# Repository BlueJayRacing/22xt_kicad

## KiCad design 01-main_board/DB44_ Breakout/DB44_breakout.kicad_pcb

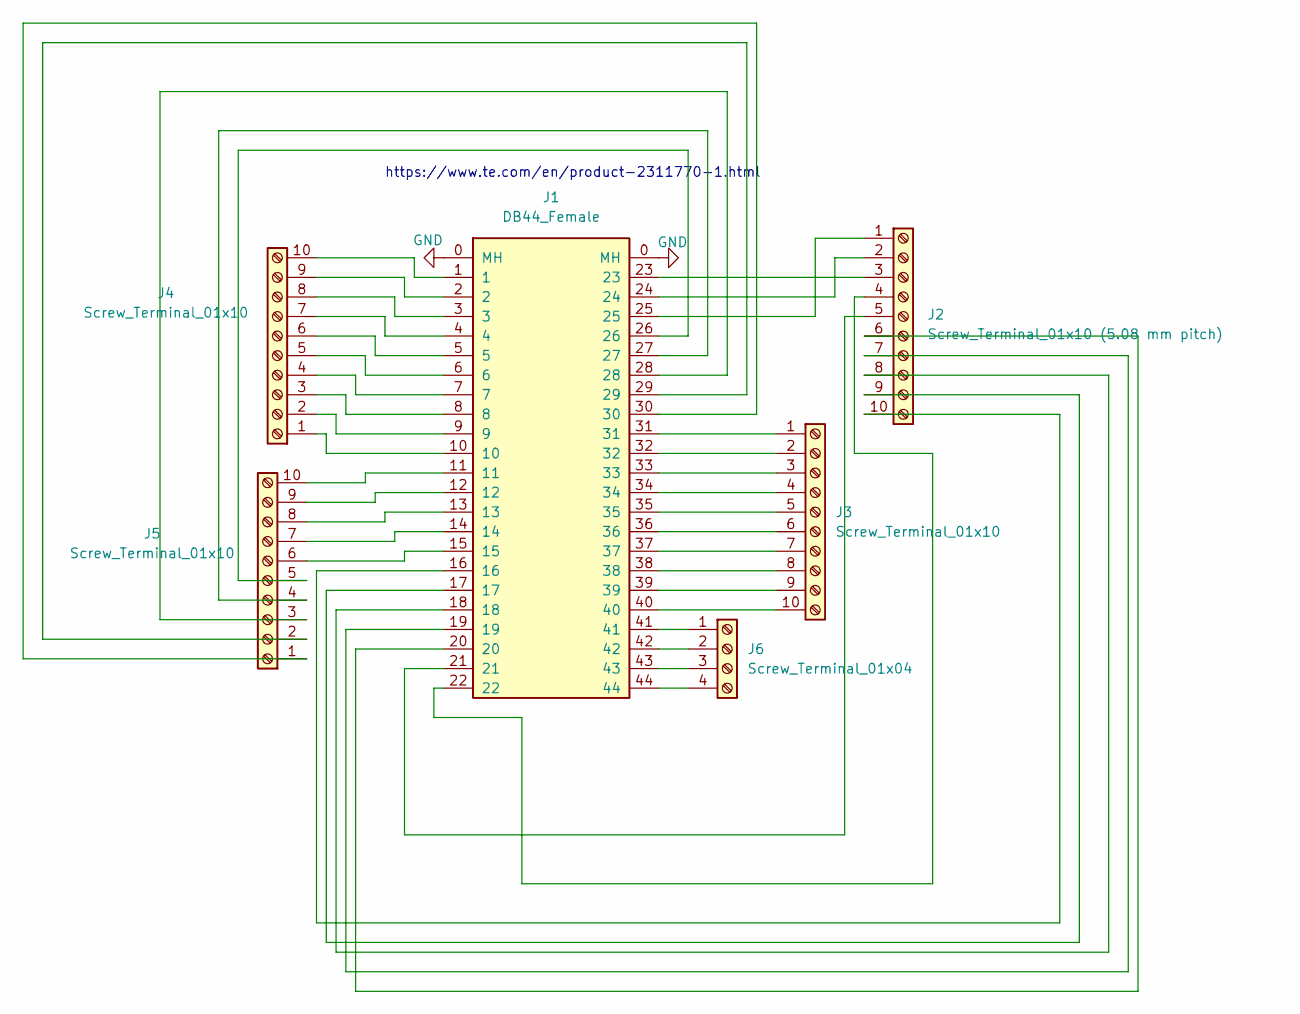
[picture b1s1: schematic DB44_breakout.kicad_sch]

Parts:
J1: DB44_Female; female-DB44-TE-2311770-1
J2: Screw_Terminal_01x10 (5.08 mm pitch); TerminalBlock_RND_205-00240_1x10_P5.08mm_Horizontal
J3, J4, J5: Screw_Terminal_01x10; TerminalBlock_RND_205-00240_1x10_P5.08mm_Horizontal
J6: Screw_Terminal_01x04; TerminalBlock_RND_205-00234_1x04_P5.08mm_Horizontal

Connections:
GND: J1.0 (MH)
unnamed: J1.25, J2.1
unnamed: J1.24, J2.2
unnamed: J1.23, J2.3
unnamed: J1.22, J2.4
unnamed: J1.21, J2.5
unnamed: J1.20, J2.6
unnamed: J1.19, J2.7
unnamed: J1.18, J2.8
unnamed: J1.17, J2.9
unnamed: J1.16, J2.10
unnamed: J1.31, J3.1
unnamed: J1.32, J3.2
unnamed: J1.33, J3.3
unnamed: J1.34, J3.4
unnamed: J1.35, J3.5
unnamed: J1.36, J3.6
unnamed: J1.37, J3.7
unnamed: J1.38, J3.8
unnamed: J1.39, J3.9
unnamed: J1.40, J3.10
unnamed: J1.10, J4.1
unnamed: J1.9, J4.2
unnamed: J1.8, J4.3
unnamed: J1.7, J4.4
unnamed: J1.6, J4.5
unnamed: J1.5, J4.6
unnamed: J1.4, J4.7
unnamed: J1.3, J4.8
unnamed: J1.2, J4.9
unnamed: J1.1, J4.10
unnamed: J1.30, J5.1
unnamed: J1.29, J5.2
unnamed: J1.28, J5.3
unnamed: J1.27, J5.4
unnamed: J1.26, J5.5
unnamed: J1.15, J5.6
unnamed: J1.14, J5.7
unnamed: J1.13, J5.8
unnamed: J1.12, J5.9
unnamed: J1.11, J5.10
unnamed: J1.41, J6.1
unnamed: J1.42, J6.2
unnamed: J1.43, J6.3
unnamed: J1.44, J6.4

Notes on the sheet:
https://www.te.com/en/product-2311770-1.html

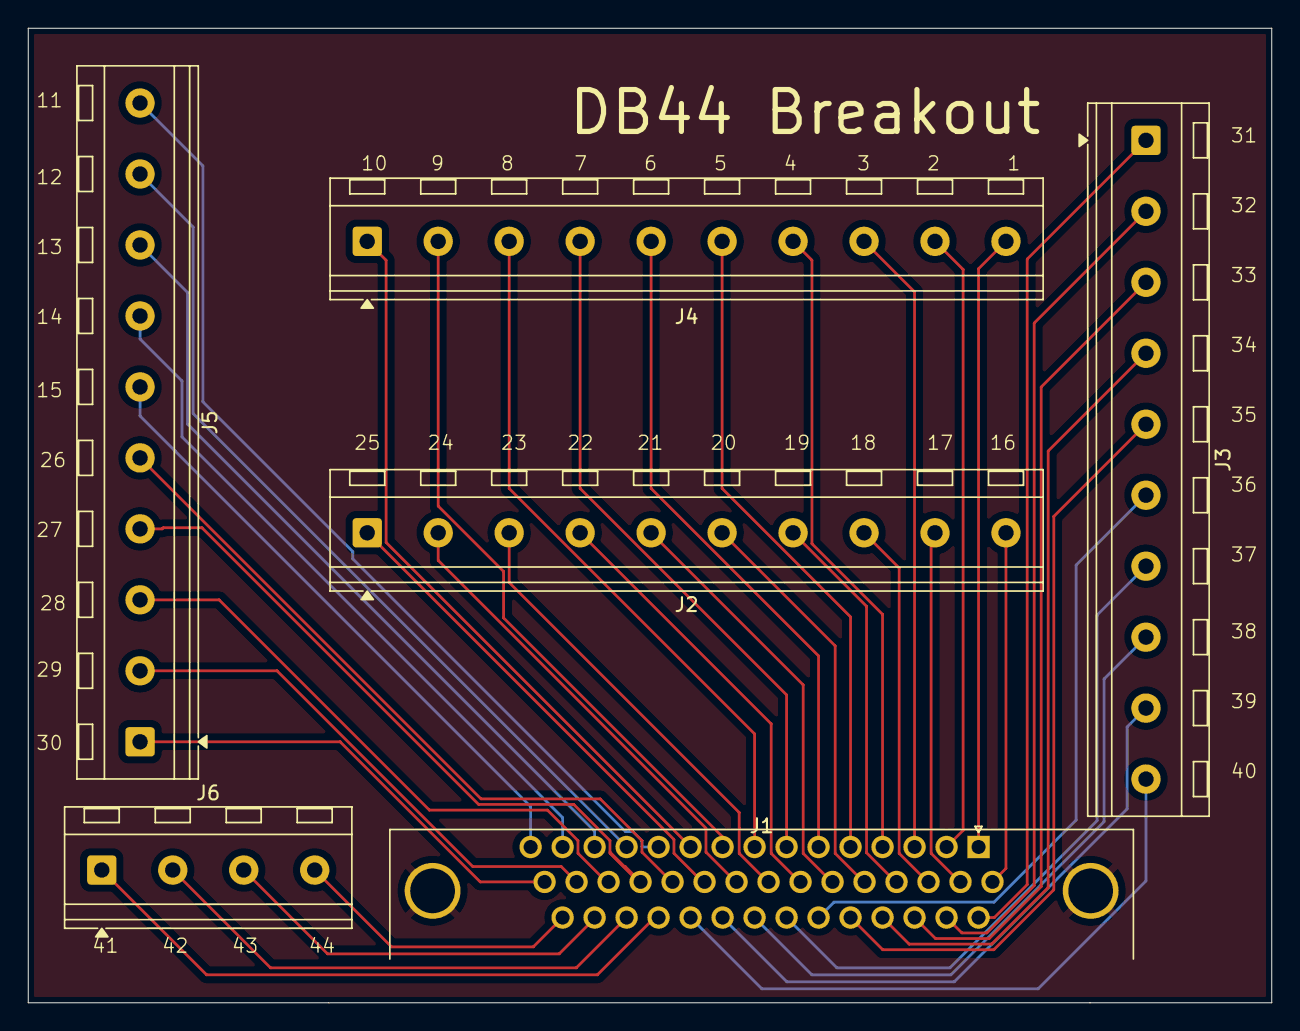
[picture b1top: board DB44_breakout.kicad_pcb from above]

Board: 2 copper layers, 89.0 x 69.8 mm, 6 parts (0 on the bottom side), 44 nets.

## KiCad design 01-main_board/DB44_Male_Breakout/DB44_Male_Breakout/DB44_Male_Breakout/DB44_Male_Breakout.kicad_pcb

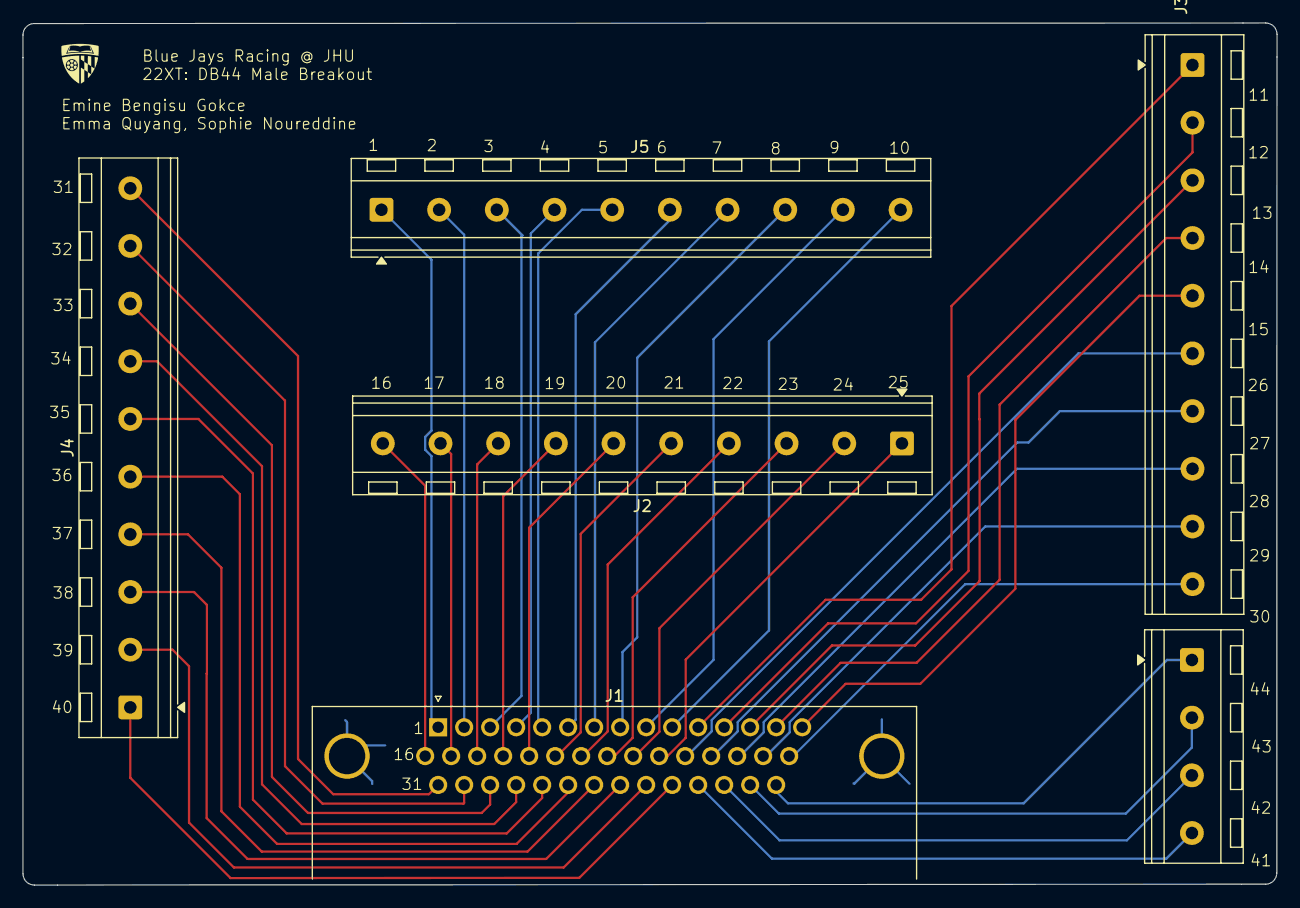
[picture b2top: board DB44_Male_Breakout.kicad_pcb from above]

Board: 2 copper layers, 110.4 x 75.9 mm, 6 parts (0 on the bottom side), 44 nets.

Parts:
J1: DB44_Male; DSUB-44-HD_Pins_Horizontal_P2.29x2.54mm_EdgePinOffset8.35mm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
J2, J3, J4, J5: Screw_Terminal_01x10; TerminalBlock_RND_205-00240_1x10_P5.08mm_Horizontal
J6: Screw_Terminal_01x04; TerminalBlock_RND_205-00234_1x04_P5.08mm_Horizontal

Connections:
3V3: J1.16, J2.10
3V3_T: J1.17, J2.9
5V: J1.35, J4.6
5V_1: J1.36, J4.5
5V_REF: J1.38, J4.3
11V1: J1.8, J5.8
11V1_1: J1.23, J2.3
AGND: J1.39, J4.2
AGND_1: J1.40, J4.1
AGND_2: J1.41, J6.4
AGND_3: J1.42, J6.3
AN1: J1.13, J3.3
AN2: J1.12, J3.2
AN3: J1.11, J3.1
AN4: J1.10, J5.10
AN5: J1.9, J5.9
AN6: J1.28, J3.8
AN7: J1.27, J3.7
AN8: J1.26, J3.6
AN9: J1.25, J2.1
AN10: J1.24, J2.2
B-: J1.37, J4.4
CANH: J1.1, J5.1
CANL: J1.2, J5.2
D1: J1.7, J5.7
D2: J1.6, J5.6
D3: J1.5, J5.5
D4: J1.22, J2.4
D5: J1.21, J2.5
D6: J1.20, J2.6
DGND: J1.31, J4.10
DGND_1: J1.32, J4.9
DGND_2: J1.33, J4.8
DGND_3: J1.34, J4.7
GP/LNT1: J1.19, J2.7
GP/LNT2: J1.18, J2.8
I2C_SCL: J1.3, J5.3
I2C_SDA: J1.4, J5.4
QS1+ (2V5R): J1.43, J6.2
QS1F-: J1.29, J3.9
QS1S-: J1.14, J3.4
QS2+ (2V5R): J1.44, J6.1
QS2F-: J1.30, J3.10
QS2S-: J1.15, J3.5

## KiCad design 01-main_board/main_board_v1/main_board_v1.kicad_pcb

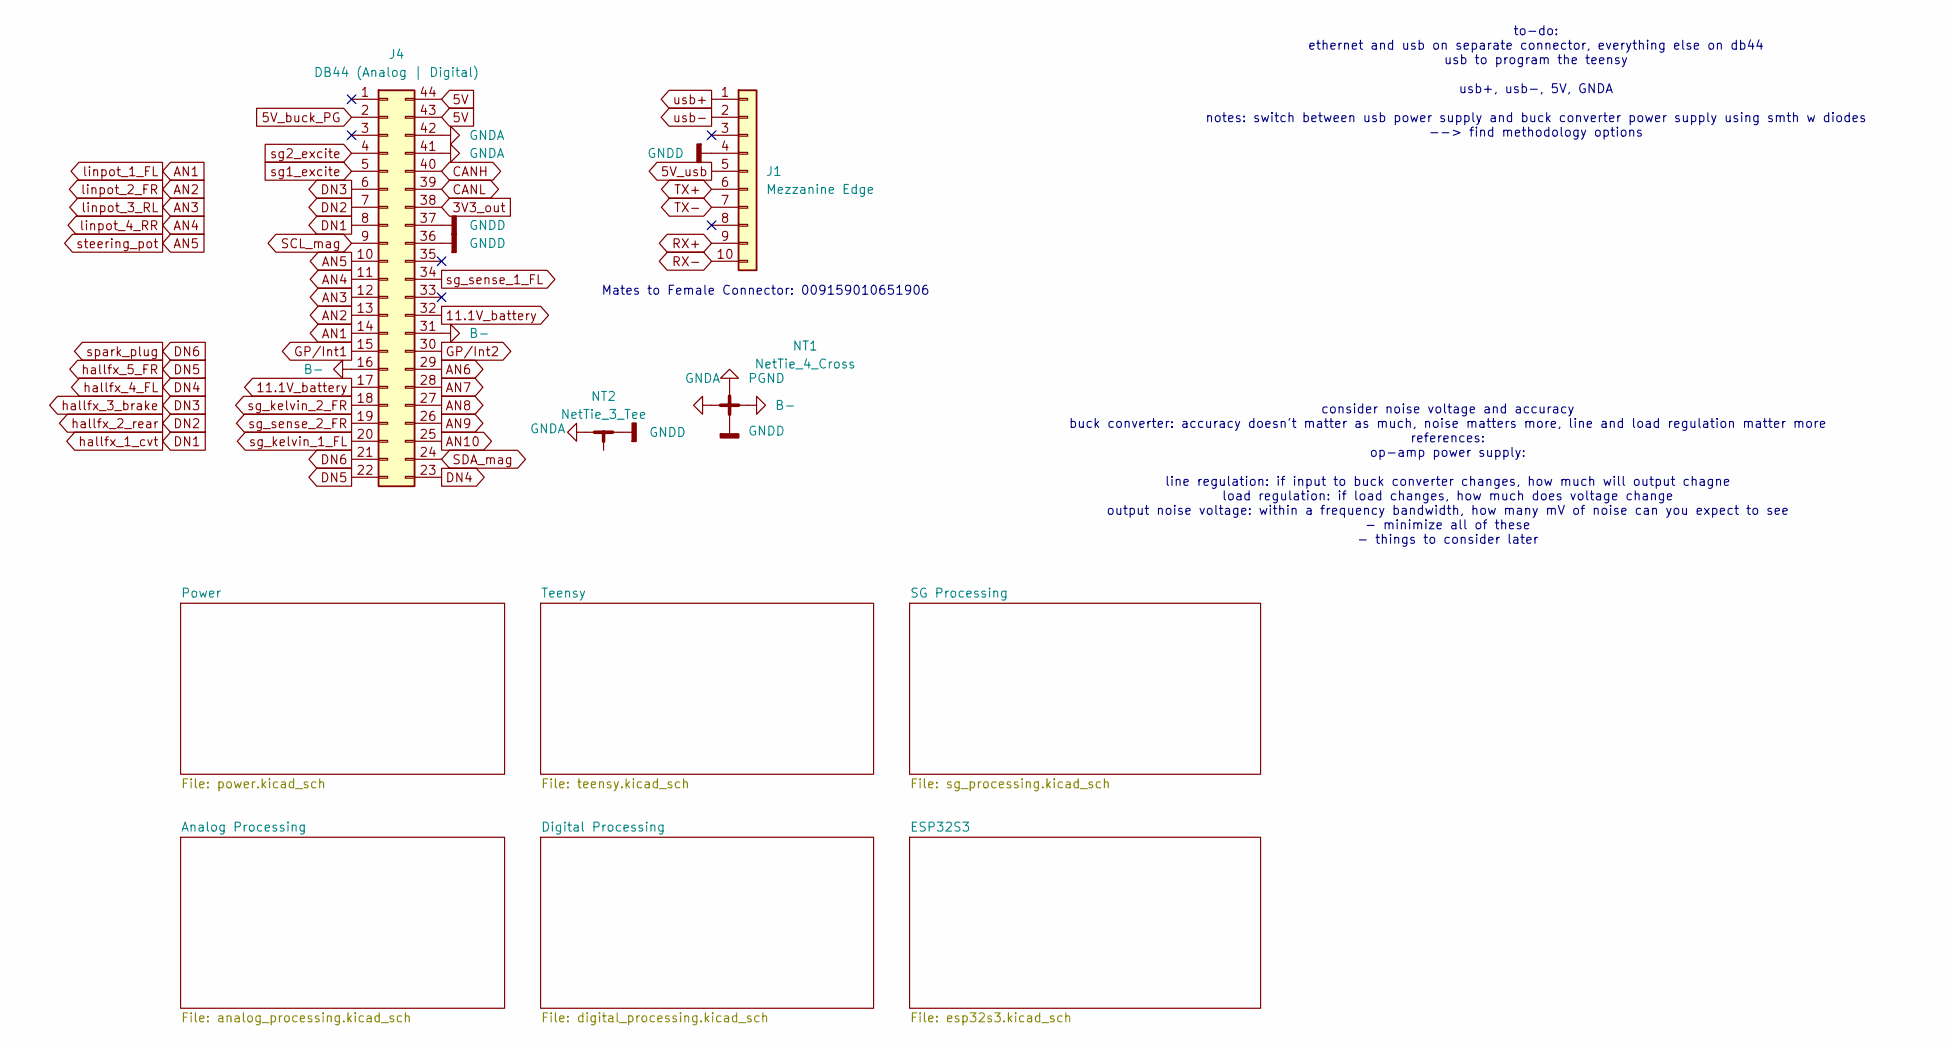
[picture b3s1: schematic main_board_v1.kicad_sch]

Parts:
J1: Mezzanine Edge; Double Sided Mezzanine Card Edge_Edge Side
J4: DB44 (Analog | Digital); aaren_mouser_db44_screws
NT1: NetTie_4_Cross; NetTie-4_SMD_Pad0.5mm
NT2: NetTie_3_Tee; NetTie-2_SMD_Pad0.5mm

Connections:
2V5: J4.4, J4.5; also elsewhere on the board
3V3_out: J4.38; also elsewhere on the board
5V: J4.43, J4.44; also elsewhere on the board
5V_buck_PG: J4.2; also elsewhere on the board
5V_usb: J1.5; also elsewhere on the board
11.1V_battery: J4.17, J4.32; also elsewhere on the board
AN1: J4.14; also elsewhere on the board
AN2: J4.13; also elsewhere on the board
AN3: J4.12; also elsewhere on the board
AN4: J4.11; also elsewhere on the board
AN5: J4.10; also elsewhere on the board
AN6: J4.29; also elsewhere on the board
AN7: J4.28; also elsewhere on the board
AN8: J4.27; also elsewhere on the board
AN9: J4.26; also elsewhere on the board
AN10: J4.25; also elsewhere on the board
B-: J4.16, J4.31, NT1.2
CANH: J4.40; also elsewhere on the board
CANL: J4.39; also elsewhere on the board
DN1: J4.8; also elsewhere on the board
DN2: J4.7; also elsewhere on the board
DN3: J4.6; also elsewhere on the board
DN4: J4.23; also elsewhere on the board
DN5: J4.22; also elsewhere on the board
DN6: J4.21; also elsewhere on the board
GP/Int1: J4.15; also elsewhere on the board
GP/Int2: J4.30; also elsewhere on the board
PGND: NT1.3; also elsewhere on the board
RX+: J1.9; also elsewhere on the board
RX-: J1.10; also elsewhere on the board
SCL_mag: J4.9; also elsewhere on the board
SDA_mag: J4.24; also elsewhere on the board
TX+: J1.6; also elsewhere on the board
TX-: J1.7; also elsewhere on the board
sg1+: J4.20; also elsewhere on the board
sg2+: J4.18; also elsewhere on the board
sg_sense_1_FL: J4.34; also elsewhere on the board
sg_sense_2_FR: J4.19; also elsewhere on the board
usb+: J1.1; also elsewhere on the board
usb-: J1.2; also elsewhere on the board

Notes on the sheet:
consider noise voltage and accuracy buck converter: accuracy doesn't matter as much, noise matters more, line and load regulation matter more references: op-amp power supply: line regulation: if input to buck converter changes, how much will output chagne load regulation: if load changes, how much 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
to-do: ethernet and usb on separate connector, everything else on db44 usb to program the teensy usb+, usb-, 5V, GNDA notes: switch between usb power supply and buck converter power supply using smth w diodes --> find methodology options
Mates to Female Connector: 009159010651906

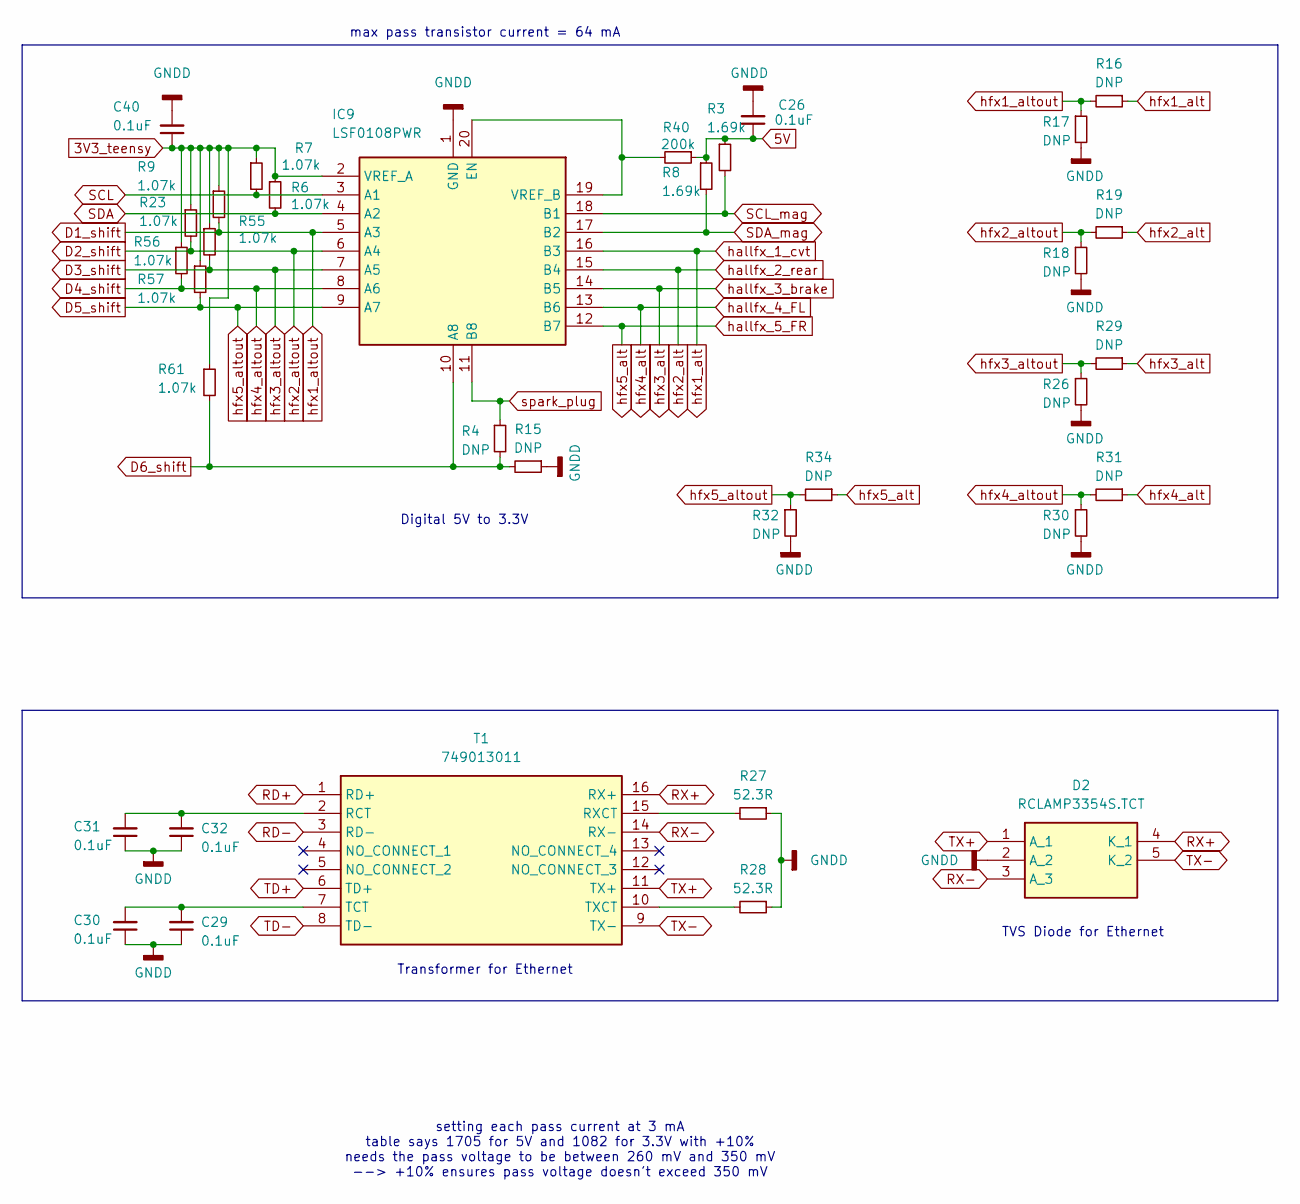
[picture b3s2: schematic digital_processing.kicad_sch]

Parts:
C26, C29, C30, C31, C32, C40: 0.1uF; C_0402_1005Metric
D2: RCLAMP3354S.TCT; SOT-23-5; Mouser Part Number 947-RCLAMP3354S.TCT
IC9: LSF0108PWR; SOP65P640X120-20N; Mouser Part Number 595-LSF0108RKSR
R3, R8: 1.69k; R_0402_1005Metric
R4, R15, R16, R17, R18, R19, R26, R29, R30, R31, R32, R34: DNP; R_0402_1005Metric
R6, R7, R9, R23, R55, R56, R57, R61: 1.07k; R_0402_1005Metric
R27, R28: 52.3R; R_0402_1005Metric
R40: 200k; R_0402_1005Metric
T1: 749013011; Mouser Part Number 710-749013011

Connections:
3V3_teensy: C40.1, IC9.2 (VREF_A), R6.1, R7.1, R9.1, R23.1, R55.1, R56.1, R57.1, R61.1; also elsewhere on the board
5V: C26.1, R3.1, R8.1, R40.1; also elsewhere on the board
D1_shift: IC9.5 (A3), R9.2, R16.2, R17.1; also elsewhere on the board
D2_shift: IC9.6 (A4), R18.1, R19.2, R23.2; also elsewhere on the board
D3_shift: IC9.7 (A5), R26.1, R29.2, R55.2; also elsewhere on the board
D4_shift: IC9.8 (A6), R30.1, R31.2, R56.2; also elsewhere on the board
D5_shift: IC9.9 (A7), R32.1, R34.2, R57.2; also elsewhere on the board
D6_shift: IC9.10 (A8), R4.2, R15.2, R61.2; also elsewhere on the board
DN1: IC9.16 (B3), R16.1; also elsewhere on the board
DN2: IC9.15 (B4), R19.1; also elsewhere on the board
DN3: IC9.14 (B5), R29.1; also elsewhere on the board
DN4: IC9.13 (B6), R31.1; also elsewhere on the board
DN5: IC9.12 (B7), R34.1; also elsewhere on the board
DN6: IC9.11 (B8), R4.1; also elsewhere on the board
unnamed: IC9.19 (VREF_B), IC9.20 (EN), R40.2
unnamed: C31.2, C32.2, T1.2 (RCT)
unnamed: R27.2, T1.15 (RXCT)
unnamed: C29.2, C30.2, T1.7 (TCT)
unnamed: R28.2, T1.10 (TXCT)
RD+: T1.1 (RD+); also elsewhere on the board
RD-: T1.3 (RD-); also elsewhere on the board
RX+: D2.4 (K_1), T1.16 (RX+); also elsewhere on the board
RX-: D2.3 (A_3), T1.14 (RX-); also elsewhere on the board
SCL: IC9.3 (A1), R7.2; also elsewhere on the board
SCL_mag: IC9.18 (B1), R3.2; also elsewhere on the board
SDA: IC9.4 (A2), R6.2; also elsewhere on the board
SDA_mag: IC9.17 (B2), R8.2; also elsewhere on the board
TD+: T1.6 (TD+); also elsewhere on the board
TD-: T1.8 (TD-); also elsewhere on the board
TX+: D2.1 (A_1), T1.11 (TX+); also elsewhere on the board
TX-: D2.5 (K_2), T1.9 (TX-); also elsewhere on the board

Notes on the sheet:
Transformer for Ethernet
max pass transistor current = 64 mA
Digital 5V to 3.3V
TVS Diode for Ethernet
setting each pass current at 3 mA table says 1705 for 5V and 1082 for 3.3V with +10% needs the pass voltage to be between 260 mV and 350 mV --> +10% ensures pass voltage doesn't exceed 350 mV

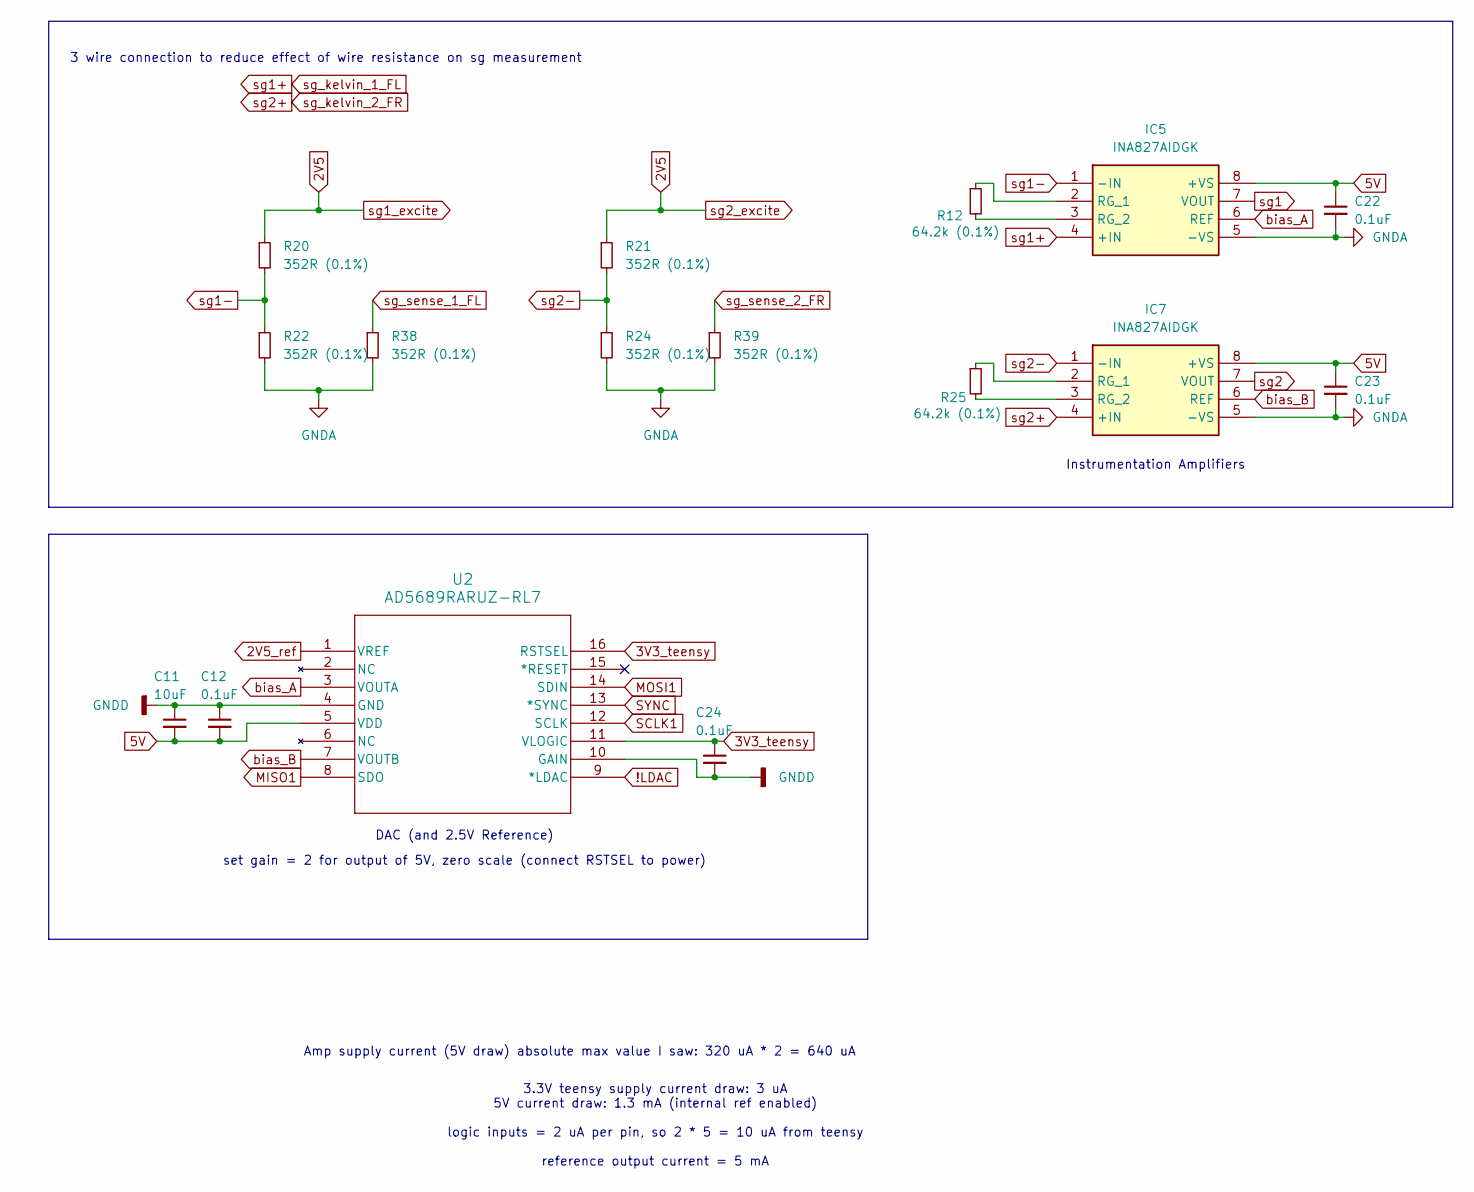
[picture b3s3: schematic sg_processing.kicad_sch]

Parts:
C11: 10uF; C_0402_1005Metric
C12, C22, C23, C24: 0.1uF; C_0402_1005Metric
IC5, IC7: INA827AIDGK; Mouser Part Number 595-INA827AIDGK
R12, R25: 64.2k (0.1%); R_0402_1005Metric
R20, R21, R22, R24, R38, R39: 352R (0.1%); R_0402_1005Metric
U2: AD5689RARUZ-RL7

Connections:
2V5: R20.1, R21.1; also elsewhere on the board
2V5_ref: U2.1 (VREF); also elsewhere on the board
3V3_teensy: C24.1, U2.11 (VLOGIC), U2.16 (RSTSEL); also elsewhere on the board
5V: C11.2, C12.2, C22.1, C23.1, IC5.8 (+VS), IC7.8 (+VS), U2.5 (VDD); also elsewhere on the board
!LDAC: U2.9 (*LDAC); also elsewhere on the board
MISO1: U2.8 (SDO); also elsewhere on the board
MOSI1: U2.14 (SDIN); also elsewhere on the board
unnamed: IC5.2 (RG_1), R12.1
unnamed: IC5.3 (RG_2), R12.2
unnamed: IC7.2 (RG_1), R25.1
unnamed: IC7.3 (RG_2), R25.2
SCLK1: U2.12 (SCLK); also elsewhere on the board
SYNC: U2.13 (*SYNC); also elsewhere on the board
bias_A: IC5.6 (REF), U2.3 (VOUTA)
bias_B: IC7.6 (REF), U2.7 (VOUTB)
sg1: IC5.7 (VOUT); also elsewhere on the board
sg1+: IC5.4 (+IN); also elsewhere on the board
sg1-: IC5.1 (-IN), R20.2, R22.1
sg2: IC7.7 (VOUT); also elsewhere on the board
sg2+: IC7.4 (+IN); also elsewhere on the board
sg2-: IC7.1 (-IN), R21.2, R24.1
sg_sense_1_FL: R38.1; also elsewhere on the board
sg_sense_2_FR: R39.1; also elsewhere on the board

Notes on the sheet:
DAC (and 2.5V Reference)
Amp supply current (5V draw) absolute max value I saw: 320 uA * 2 = 640 uA
3.3V teensy supply current draw: 3 uA 5V current draw: 1.3 mA (internal ref enabled) logic inputs = 2 uA per pin, so 2 * 5 = 10 uA from teensy reference output current = 5 mA
set gain = 2 for output of 5V, zero scale (connect RSTSEL to power)
Instrumentation Amplifiers
3 wire connection to reduce effect of wire resistance on sg measurement

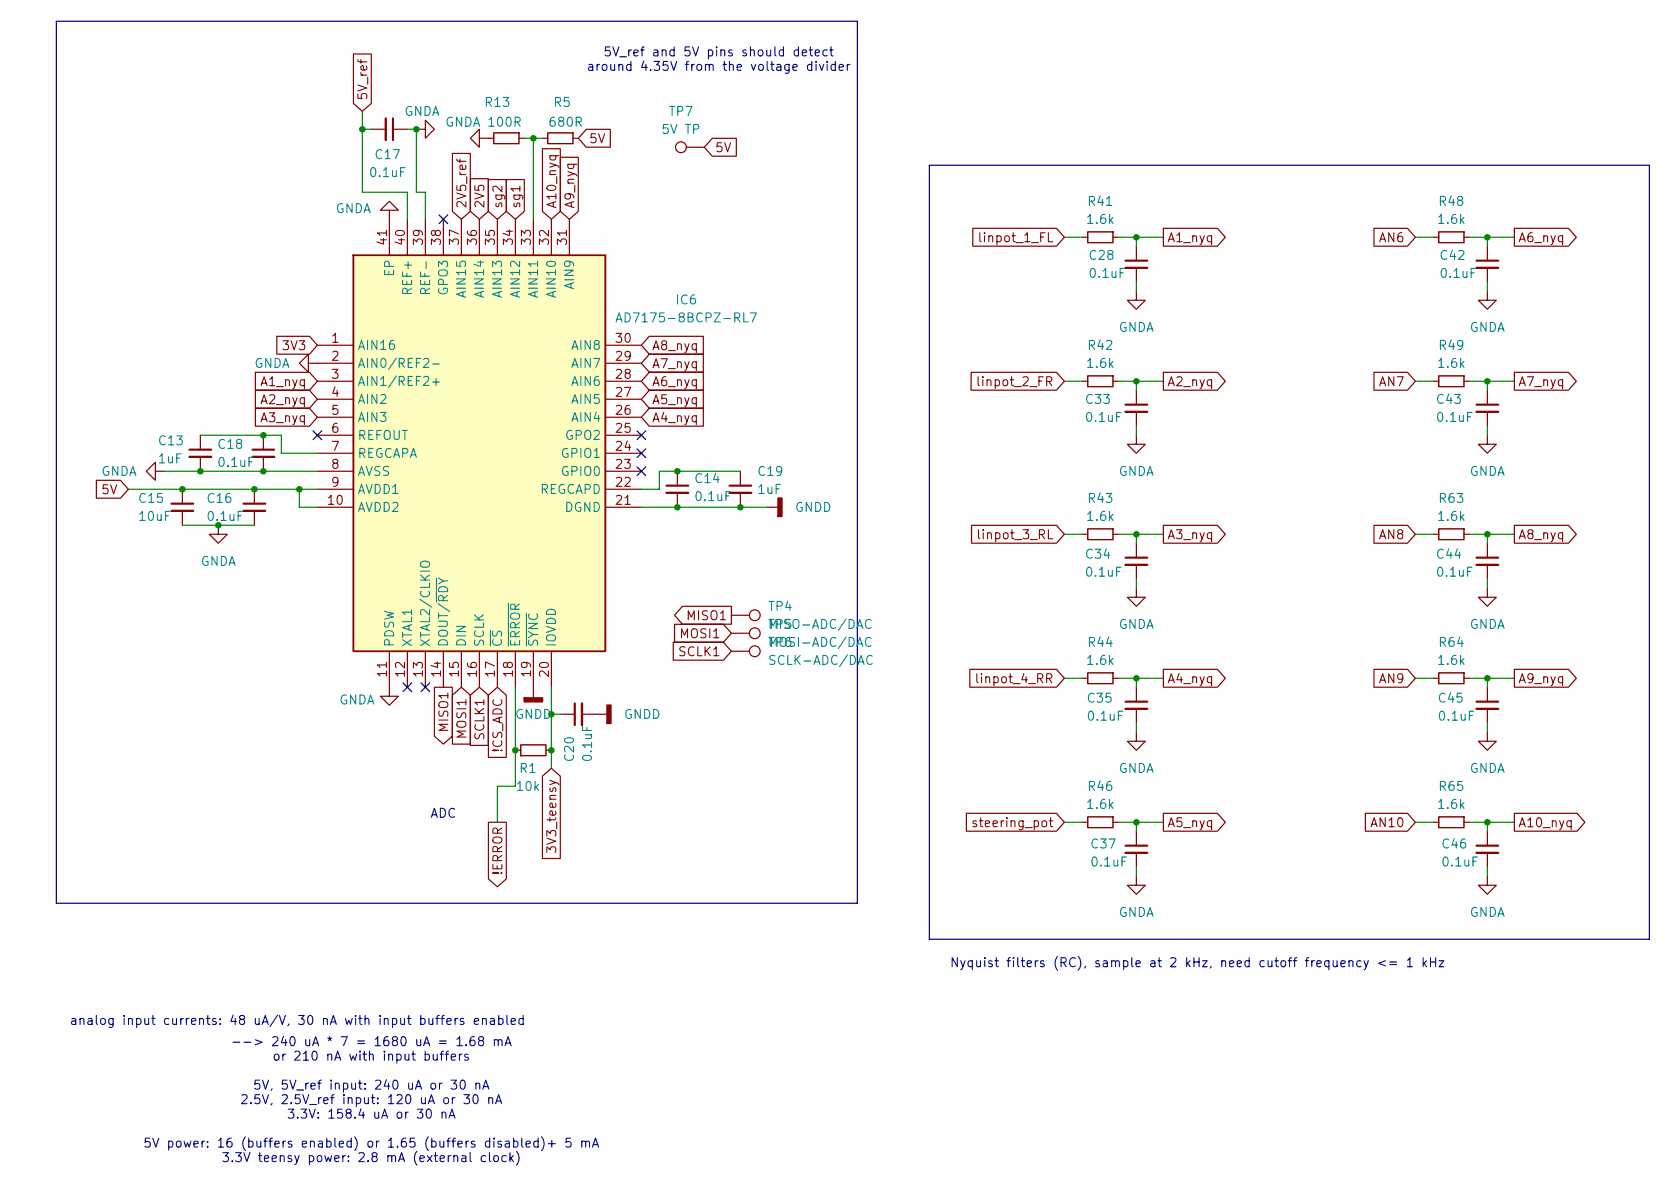
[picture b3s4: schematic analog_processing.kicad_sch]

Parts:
C13, C19: 1uF; C_0402_1005Metric
C14, C16, C17, C18, C20, C28, C33, C34, C35, C37, C42, C43, C44, C45, C46: 0.1uF; C_0402_1005Metric
C15: 10uF; C_0402_1005Metric
IC6: AD7175-8BCPZ-RL7; QFN50P600X600X80-41N-D; Mouser Part Number 584-AD7175-8BCPZ-RL7
R1: 10k; R_0402_1005Metric
R5: 680R; R_0402_1005Metric
R13: 100R; R_0402_1005Metric
R41, R42, R43, R44, R46, R48, R49, R63, R64, R65: 1.6k; R_0402_1005Metric
TP4: MISO-ADC/DAC; TestPoint_Pad_1.0x1.0mm
TP5: MOSI-ADC/DAC; TestPoint_Pad_1.0x1.0mm
TP6: SCLK-ADC/DAC; TestPoint_Pad_1.0x1.0mm
TP7: 5V TP; TestPoint_Pad_1.0x1.0mm

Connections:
2V5: IC6.36 (AIN14); also elsewhere on the board
2V5_ref: IC6.37 (AIN15); also elsewhere on the board
3V3: IC6.1 (AIN16); also elsewhere on the board
3V3_teensy: C20.1, IC6.20 (IOVDD), R1.2; also elsewhere on the board
5V: C15.1, C16.1, IC6.9 (AVDD1), IC6.10 (AVDD2), R5.1, TP7.1; also elsewhere on the board
5V_ref: C17.2, IC6.40 (REF+); also elsewhere on the board
!CS_ADC: IC6.17 (~CS); also elsewhere on the board
!ERROR: IC6.18 (~ERROR), R1.1; also elsewhere on the board
A1_nyq: C28.1, IC6.3 (AIN1/REF2+), R41.1
A2_nyq: C33.1, IC6.4 (AIN2), R42.1
A3_nyq: C34.1, IC6.5 (AIN3), R43.1
A4_nyq: C35.1, IC6.26 (AIN4), R44.1
A5_nyq: C37.1, IC6.27 (AIN5), R46.1
A6_nyq: C42.1, IC6.28 (AIN6), R48.1
A7_nyq: C43.1, IC6.29 (AIN7), R49.1
A8_nyq: C44.1, IC6.30 (AIN8), R63.1
A9_nyq: C45.1, IC6.31 (AIN9), R64.1
A10_nyq: C46.1, IC6.32 (AIN10), R65.1
AN1: R41.2; also elsewhere on the board
AN2: R42.2; also elsewhere on the board
AN3: R43.2; also elsewhere on the board
AN4: R44.2; also elsewhere on the board
AN5: R46.2; also elsewhere on the board
AN6: R48.2; also elsewhere on the board
AN7: R49.2; also elsewhere on the board
AN8: R63.2; also elsewhere on the board
AN9: R64.2; also elsewhere on the board
AN10: R65.2; also elsewhere on the board
MISO1: IC6.14 (DOUT/~RDY), TP4.1; also elsewhere on the board
MOSI1: IC6.15 (DIN), TP5.1; also elsewhere on the board
unnamed: IC6.33 (AIN11), R5.2, R13.1
unnamed: C13.1, C18.1, IC6.7 (REGCAPA)
unnamed: C14.1, C19.1, IC6.22 (REGCAPD)
SCLK1: IC6.16 (SCLK), TP6.1; also elsewhere on the board
sg1: IC6.34 (AIN12); also elsewhere on the board
sg2: IC6.35 (AIN13); also elsewhere on the board

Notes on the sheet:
ADC
--> 240 uA * 7 = 1680 uA = 1.68 mA or 210 nA with input buffers 5V, 5V_ref input: 240 uA or 30 nA 2.5V, 2.5V_ref input: 120 uA or 30 nA 3.3V: 158.4 uA or 30 nA 5V power: 16 (buffers enabled) or 1.65 (buffers disabled)+ 5 mA 3.3V teensy power: 2.8 mA (external clock)
analog input currents: 48 uA/V, 30 nA with input buffers enabled
Nyquist filters (RC), sample at 2 kHz, need cutoff frequency <= 1 kHz
5V_ref and 5V pins should detect around 4.35V from the voltage divider

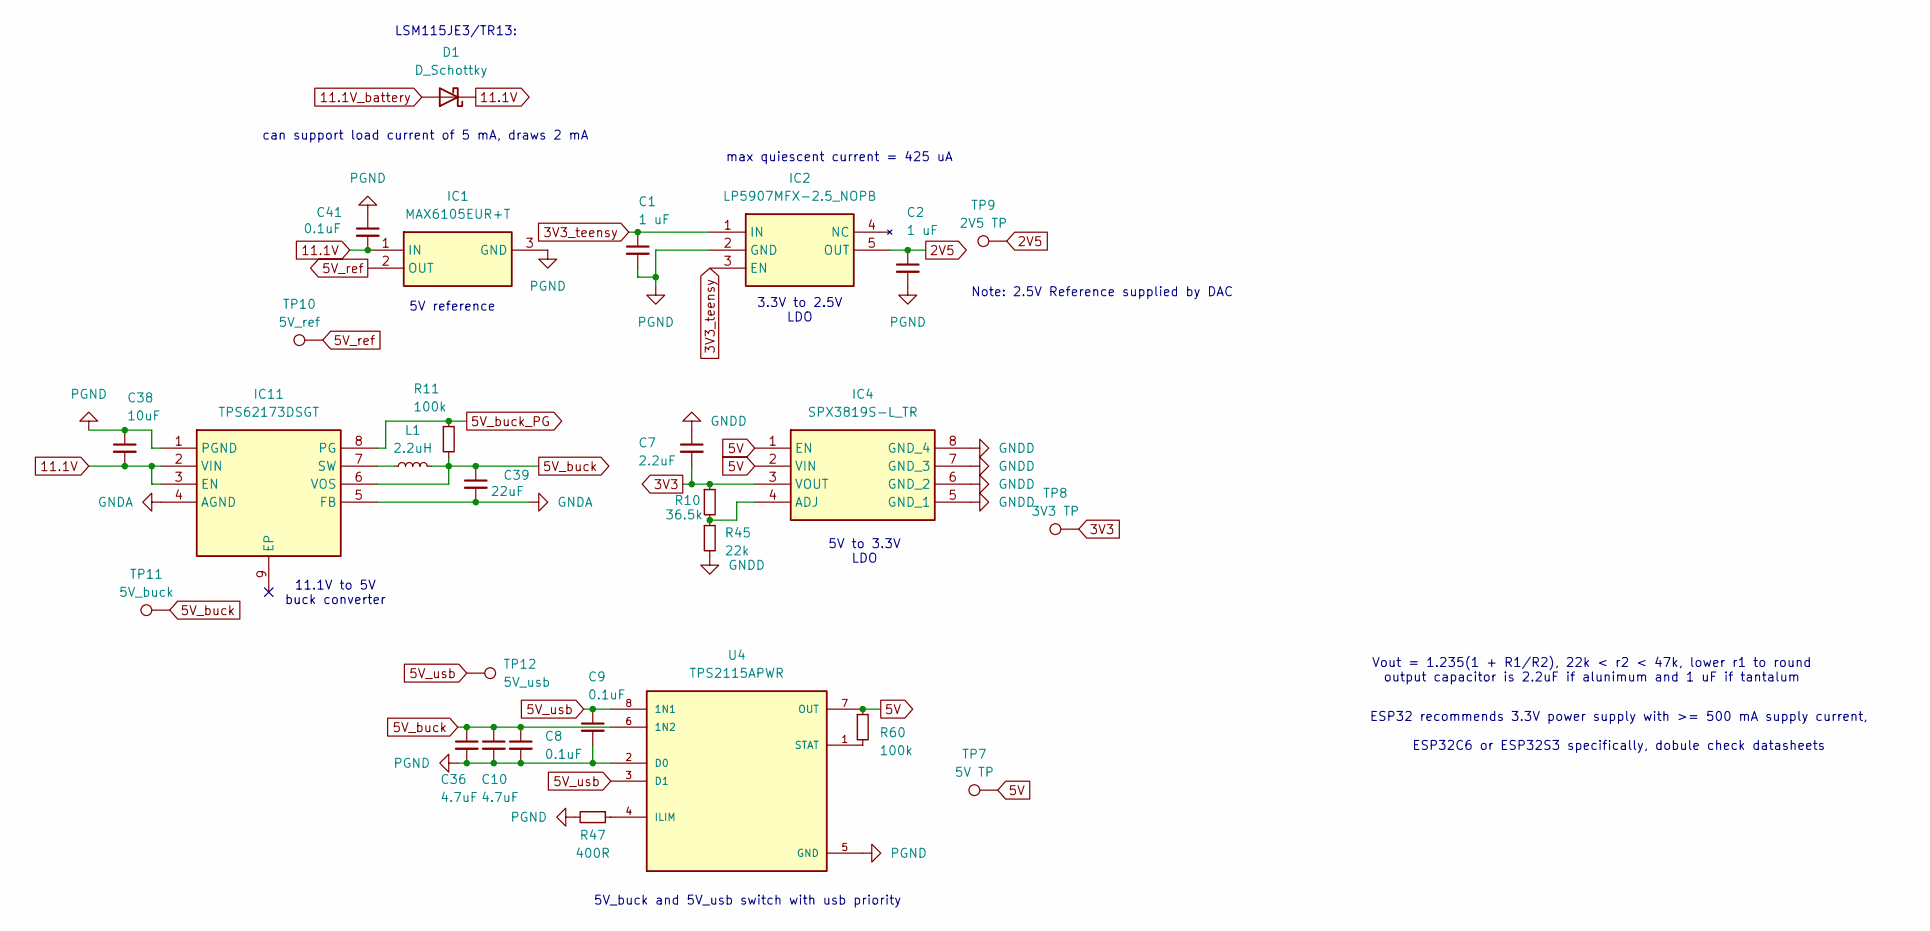
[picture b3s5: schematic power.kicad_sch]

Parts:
C1, C2: 1 uF; C_0402_1005Metric
C7: 2.2uF; C_0402_1005Metric
C8, C9, C41: 0.1uF; C_0402_1005Metric
C10, C36: 4.7uF; C_0402_1005Metric
C38: 10uF; C_0402_1005Metric
C39: 22uF; C_0402_1005Metric
D1: D_Schottky; DO-214BA_MCH
IC1: MAX6105EUR+T; SOT-23-3; Mouser Part Number 700-MAX6105EURT
IC2: LP5907MFX-2.5_NOPB; SOT-23-5; Mouser Part Number 595-LP5907MFX2.5NOPB
IC4: SPX3819S-L_TR; SOIC127P600X175-8N; Mouser Part Number 701-SPX3819S-L/TR
IC11: TPS62173DSGT; SON50P200X200X80-9N; Mouser Part Number 595-TPS62173DSGT
L1: 2.2uH; L_0402_1005Metric
R10: 36.5k; R_0402_1005Metric
R11, R60: 100k; R_0402_1005Metric
R45: 22k; R_0402_1005Metric
R47: 400R; R_0402_1005Metric
TP7: 5V TP; TestPoint_Pad_1.0x1.0mm
TP8: 3V3 TP; TestPoint_Pad_1.0x1.0mm
TP9: 2V5 TP; TestPoint_Pad_1.0x1.0mm
TP10: 5V_ref; TestPoint_Pad_1.0x1.0mm
TP11: 5V_buck; TestPoint_Pad_1.0x1.0mm
TP12: 5V_usb; TestPoint_Pad_1.0x1.0mm
U4: TPS2115APWR; SOP65P640X120-8N; PARTREV F

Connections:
2V5: C2.1, IC2.5 (OUT), TP9.1; also elsewhere on the board
3V3: C7.2, IC4.3 (VOUT), R10.1, TP8.1; also elsewhere on the board
3V3_teensy: C1.1, IC2.1 (IN), IC2.3 (EN); also elsewhere on the board
5V: IC4.1 (EN), IC4.2 (VIN), R60.1, TP7.1, U4.7 (OUT); also elsewhere on the board
5V_buck: C8.1, C10.1, C36.1, C39.1, IC11.6 (VOS), L1.2, R11.2, TP11.1, U4.6 (1N2)
5V_buck_PG: IC11.8 (PG), R11.1; also elsewhere on the board
5V_ref: IC1.2 (OUT), TP10.1; also elsewhere on the board
5V_usb: C9.1, TP12.1, U4.3 (D1), U4.8 (1N1); also elsewhere on the board
11.1V: C38.2, C41.2, D1.1 (K), IC1.1 (IN), IC11.2 (VIN), IC11.3 (EN)
11.1V_battery: D1.2 (A); also elsewhere on the board
unnamed: IC4.4 (ADJ), R10.2, R45.1
unnamed: IC11.7 (SW), L1.1
unnamed: R47.1, U4.4 (ILIM)
unnamed: R60.2, U4.1 (STAT)
PGND: C1.2, C2.2, C8.2, C9.2, C10.2, C36.2, C38.1, C41.1, IC1.3 (GND), IC2.2 (GND), IC11.1 (PGND), R47.2, U4.2 (D0), U4.5 (GND); also elsewhere on the board

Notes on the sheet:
LSM115JE3/TR13:
5V to 3.3V LDO
11.1V to 5V buck converter
5V_buck and 5V_usb switch with usb priority
max quiescent current = 425 uA
ESP32 recommends 3.3V power supply with >= 500 mA supply current, ESP32C6 or ESP32S3 specifically, dobule check datasheets
5V reference
can support load current of 5 mA, draws 2 mA
Vout = 1.235(1 + R1/R2), 22k < r2 < 47k, lower r1 to round output capacitor is 2.2uF if alunimum and 1 uF if tantalum
3.3V to 2.5V LDO
Note: 2.5V Reference supplied by DAC
